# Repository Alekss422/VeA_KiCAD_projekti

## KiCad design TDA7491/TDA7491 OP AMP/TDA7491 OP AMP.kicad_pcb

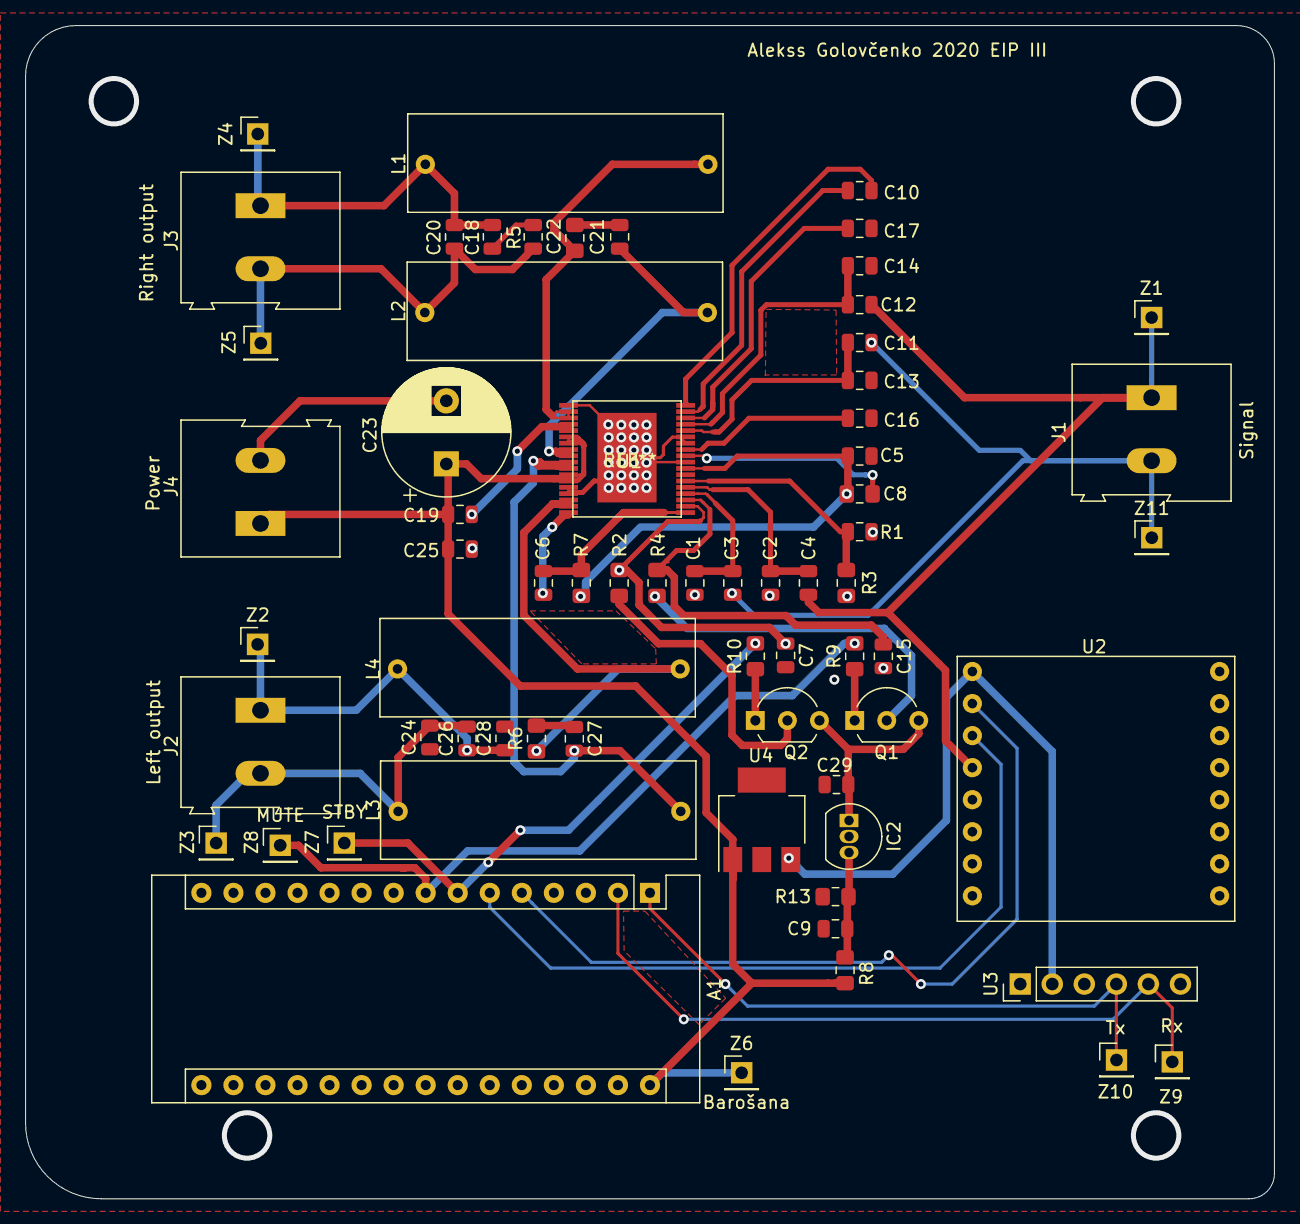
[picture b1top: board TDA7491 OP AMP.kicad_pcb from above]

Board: 2 copper layers, 99.0 x 93.0 mm, 67 parts (0 on the bottom side), 43 nets.

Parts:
A1: Arduino_Nano_v2.x; Arduino_Nano
C1, C2, C13, C14: 1 nF; C_0805_2012Metric
C3, C4, C11, C12: 470 nF; C_0805_2012Metric
C5, C6, C8, C9, C10, C18, C19, C22, C24, C25, C28: 100nF; C_0805_2012Metric
C7: 2.2nF; C_0805_2012Metric
C15, C29: 2.2uF; C_0805_2012Metric
C16, C17: 1uF; C_0805_2012Metric
C20, C26: 220nF; C_0805_2012Metric
C21, C27: 330pF; C_0805_2012Metric
C23: 1000uF; CP_Radial_D10.0mm_P5.00mm
IC2: 3V3; TO-92_Inline
J1: Signal; TerminalBlock_Altech_AK300-2_P5.00mm
J2: L-output; TerminalBlock_Altech_AK300-2_P5.00mm
J3: R-output; TerminalBlock_Altech_AK300-2_P5.00mm
J4: Power 12V; TerminalBlock_Altech_AK300-2_P5.00mm
L1, L2, L3, L4: 33uH; Spole
Q1, Q2: npn; TO-92L_Inline_Wide
R1: 100K; R_0805_2012Metric_Pad1.15x1.40mm_HandSolder
R2, R4: 33K; R_0805_2012Metric_Pad1.15x1.40mm_HandSolder
R3: 39K; R_0805_2012Metric_Pad1.15x1.40mm_HandSolder
R5, R6, R7: 22R; R_0805_2012Metric_Pad1.15x1.40mm_HandSolder
R8: 2.2K; R_0805_2012Metric_Pad1.15x1.40mm_HandSolder
R9, R10: R_Small; R_0805_2012Metric_Pad1.15x1.40mm_HandSolder
R13: 9.1K; R_0805_2012Metric_Pad1.15x1.40mm_HandSolder
U1: TDA7491
U2: DFplayermini; DF_player_mini
U3: Bluetooth; PinHeader_1x06_P2.54mm_Vertical
U4: 5V_stabilizators; SOT-223-3_TabPin2
Z1: Signal; PinHeader_1x01_P2.54mm_Vertical
Z2: J2 output; PinHeader_1x01_P2.54mm_Vertical
Z3: J2 output.1; PinHeader_1x01_P2.54mm_Vertical
Z4: J3 output; PinHeader_1x01_P2.54mm_Vertical
Z5: J3 output.1; PinHeader_1x01_P2.54mm_Vertical
Z6: Barošana; PinHeader_1x01_P2.54mm_Vertical
Z7: Mode_STYB; PinHeader_1x01_P2.54mm_Vertical
Z8: Mode_MUTE; PinHeader_1x01_P2.54mm_Vertical
Z9: RX; PinHeader_1x01_P2.54mm_Vertical
Z10: TX; PinHeader_1x01_P2.54mm_Vertical
Z11: Audio input -; PinHeader_1x01_P2.54mm_Vertical

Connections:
5V: U2.1, U3.2, U4.3
/Sheet5F97E1B5/3V3: C29.1, IC2.1, Q1.3, Q2.3
Audio_input: C4.1, C12.1, J1.1, U2.4, Z1.1
Audio_input-: C3.1, C11.1, J1.2, Z11.1
B.T.Rx: A1.2, U3.5, Z9.1
B.T.Tx: A1.1, U3.4, Z10.1
D0_RX: A1.5, U2.2
D1_TX: A1.6, U2.3
GND: A1.4, A1.29, C1.1, C2.2, C5.1, C7.2, C8.2, C9.2, C13.1, C14.2, C15.2, C16.2, C17.2, C18.2, C22.1, C23.2, C24.1, C25.1, C28.2, C29.2, IC2.2, J4.2, R3.1, R13.2, U1.1, U1.14, U1.15, U1.27, U1.30, U1.31, U2.7, U2.10, U2.16, U3.3, U4.2
L2_output: C26.1, C28.1, J2.1, L4.2, Z2.1
L2_output.1: C24.2, C26.2, J2.2, L3.2, Z3.1
L3_output: C18.1, C20.1, J3.1, L1.2, Z4.1
L3_output.1: C20.2, C22.2, J3.2, L2.2, Z5.1
Mute: A1.8, R9.2, Z8.1
unnamed: C1.2, C3.2, U1.22
unnamed: C2.1, C4.2, U1.23
unnamed: C5.2, R1.2, R7.2, U1.26
unnamed: C6.1, R7.1, U1.19
unnamed: C6.2, U1.18
unnamed: C7.1, R2.1, U1.20
unnamed: C8.1, R3.2, U1.24
unnamed: C9.1, IC2.3, R8.1, R13.1
unnamed: C10.1, U1.35
unnamed: C10.2, U1.36
unnamed: C11.2, C13.2, U1.32
unnamed: C12.2, C14.1, U1.33
unnamed: C15.1, R4.1, U1.21
unnamed: C16.1, U1.29
unnamed: C17.1, U1.34
unnamed: C19.2, U1.4, U1.5
unnamed: C21.1, R5.2
unnamed: C21.2, L2.1, U1.8, U1.9
unnamed: C27.1, R6.2
unnamed: C27.2, L3.1, U1.10, U1.11
unnamed: L1.1, R5.1, U1.2, U1.3
unnamed: L4.1, R6.1, U1.16, U1.17
unnamed: Q1.1, R9.1
unnamed: Q1.2, R4.2
unnamed: Q2.1, R10.1
unnamed: Q2.2, R2.2
unnamed: R1.1, U1.28
STBY: A1.7, R10.2, Z7.1
VCC: A1.30, C19.1, C23.1, C25.2, J4.1, R8.2, U1.6, U1.7, U1.12, U1.13, U4.1, Z6.1

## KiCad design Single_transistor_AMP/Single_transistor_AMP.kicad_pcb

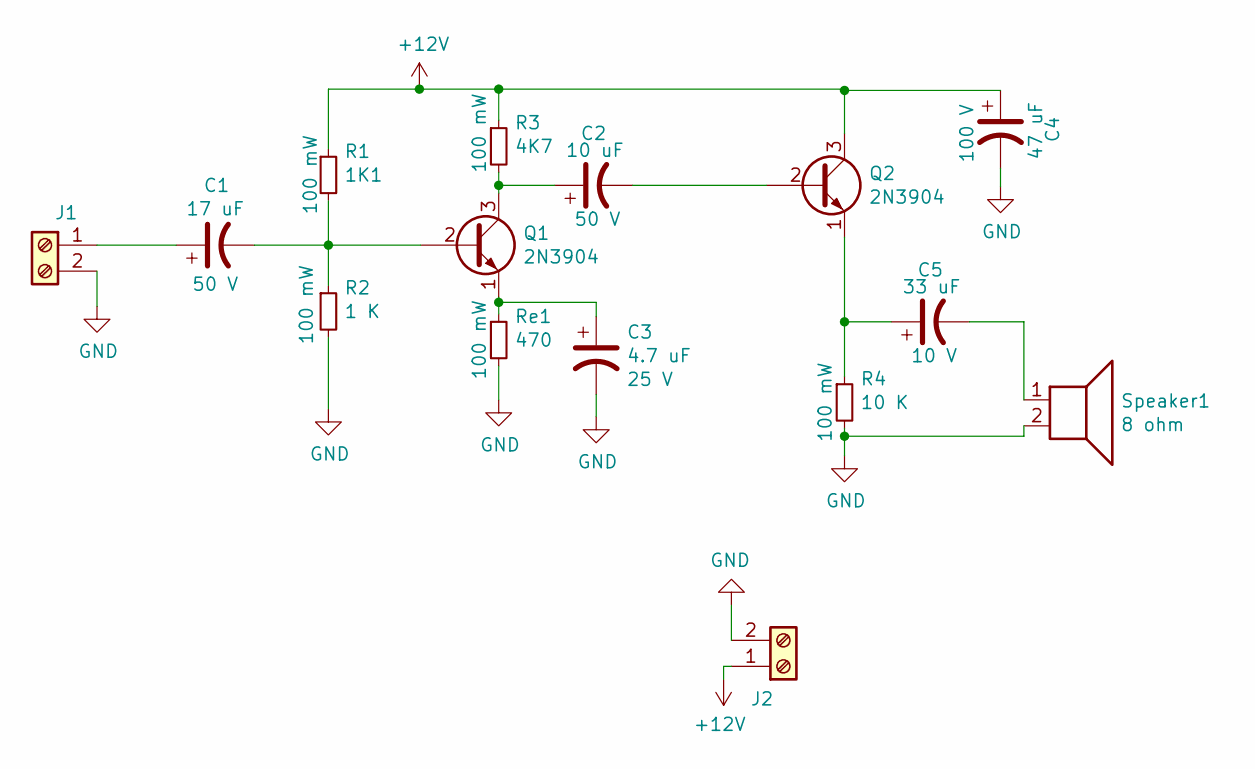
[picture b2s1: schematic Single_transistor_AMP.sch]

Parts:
C1: 17 uF; CP_Elec_6.3x9.9; Max Voltage 50 V
C2: 10 uF; CP_Elec_6.3x9.9; Max Voltage 50 V
C3: 4.7 uF; C_0805_2012Metric
C4: 47 uF; C_0805_2012Metric; Max Voltage 100 V
C5: 33 uF; C_0805_2012Metric; Max Voltage 10 V
J1: ETB06; TerminalBlock_Altech_AK300-2_P5.00mm
J2: Power; TerminalBlock_Altech_AK300-2_P5.00mm
Q1, Q2: 2N3904; TO-39-3
R1: 1K1; R_0805_2012Metric
R2: 1 K; R_0805_2012Metric
R3: 4K7; R_0805_2012Metric
R4: 10 K; R_0805_2012Metric
Re1: 470; R_0805_2012Metric
Speaker1: 8 ohm; TerminalBlock_Altech_AK300-2_P5.00mm

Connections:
+12V: C4.1, J2.1, Q2.3 (C), R1.1, R3.1
GND: C3.2, C4.2, J1.2, J2.2, R2.2, R4.2, Re1.2, Speaker1.2
unnamed: C1.1, J1.1
unnamed: C1.2, Q1.2 (B), R1.2, R2.1
unnamed: C2.1, Q1.3 (C), R3.2
unnamed: C2.2, Q2.2 (B)
unnamed: C3.1, Q1.1 (E), Re1.1
unnamed: C5.1, Q2.1 (E), R4.1
unnamed: C5.2, Speaker1.1

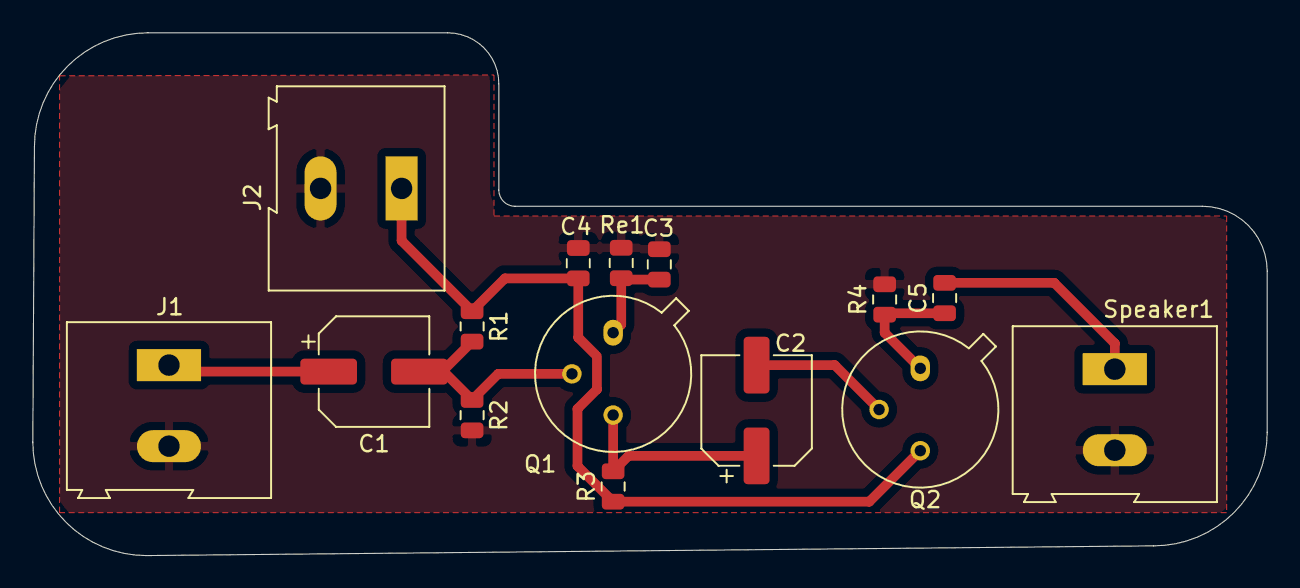
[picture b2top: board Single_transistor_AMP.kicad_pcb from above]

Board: 2 copper layers, 76.2 x 32.2 mm, 15 parts (0 on the bottom side), 9 nets.

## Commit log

2020-10-08 Pabeiks pedejais md
2020-10-12 MD 2
2020-10-14 MD_3
2020-10-26 Baterijas_MD
2020-10-26 Baterijas_ MD1.1
2020-11-17 Pedejais MD
2020-12-03 MD savienojumi
2020-12-03 plot izveide
2021-01-26 EXAM
